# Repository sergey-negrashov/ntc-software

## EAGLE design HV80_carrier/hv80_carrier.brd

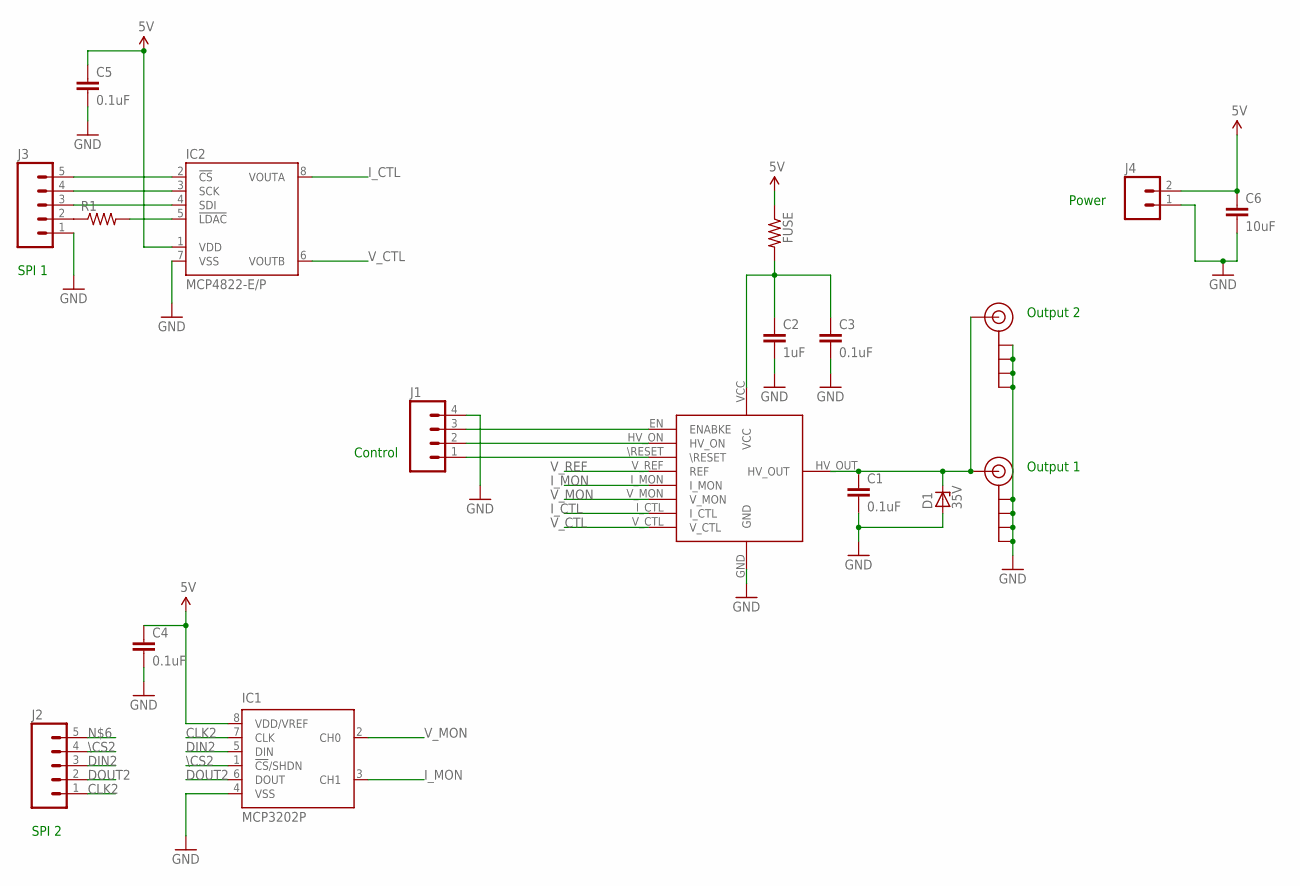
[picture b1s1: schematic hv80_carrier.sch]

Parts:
C1, C3, C4, C5: 0.1uF; 1206
C2: 1uF; 1206
C6: 10uF; 1206
D1: 35V; DO41Z10
FUSE: RESISTORPTH-1/4W; AXIAL-0.4
IC1: MCP3202P; DIL8
IC2: MCP4822-E/P; DIL08
J1: M04PTH; 1X04
J2, J3: M05PTH; 1X05
J4: M023.5MM; SCREWTERMINAL-3.5MM-2
J$1, J$2: SMA_EDGE; SMA-EDGE
R1: RESISTORPTH-1/4W; AXIAL-0.4
U$1: HV80

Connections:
5V: C4.1, C5.1, C6.1, FUSE.P$1 (1), IC1.8 (VDD/VREF), IC2.1 (VDD), J4.2
CLK2: IC1.7 (CLK), J2.1
DIN2: IC1.5 (DIN), J2.3
DOUT2: IC1.6 (DOUT), J2.2
GND: C1.2, C2.2, C3.2, C4.2, C5.2, C6.2, D1.A, IC1.4 (VSS), IC2.7 (VSS), J1.4, J3.1, J4.1, J$1.GND@0 (GND), J$1.GND@1 (GND), J$1.GND@2 (GND), J$1.GND@3 (GND), J$2.GND@0 (GND), J$2.GND@1 (GND), J$2.GND@2 (GND), J$2.GND@3 (GND), U$1.GND
I_CTL: IC2.8 (VOUTA), U$1.I_CTL
I_MON: IC1.3 (CH1), U$1.I_MON
unnamed: J1.1, U$1.\RESET
unnamed: J1.2, U$1.HV_ON
unnamed: J1.3, U$1.EN (ENABKE)
unnamed: C1.1, D1.C, J$1.SIG (SIGNAL), J$2.SIG (SIGNAL), U$1.HV_OUT
unnamed: J3.2, R1.P$1 (1)
unnamed: IC2.5 (!LDAC), R1.P$2 (2)
unnamed: C2.1, C3.1, FUSE.P$2 (2), U$1.VCC
SCK1: IC2.3 (SCK), J3.4
SDI1: IC2.4 (SDI), J3.3
V_CTL: IC2.6 (VOUTB), U$1.V_CTL
V_MON: IC1.2 (CH0), U$1.V_MON
V_REF: U$1.V_REF (REF)
\CS1: IC2.2 (!CS), J3.5
\CS2: IC1.1 (!CS!/SHDN), J2.4

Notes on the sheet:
SPI 1
SPI 2
Control
Power
Output 1
Output 2

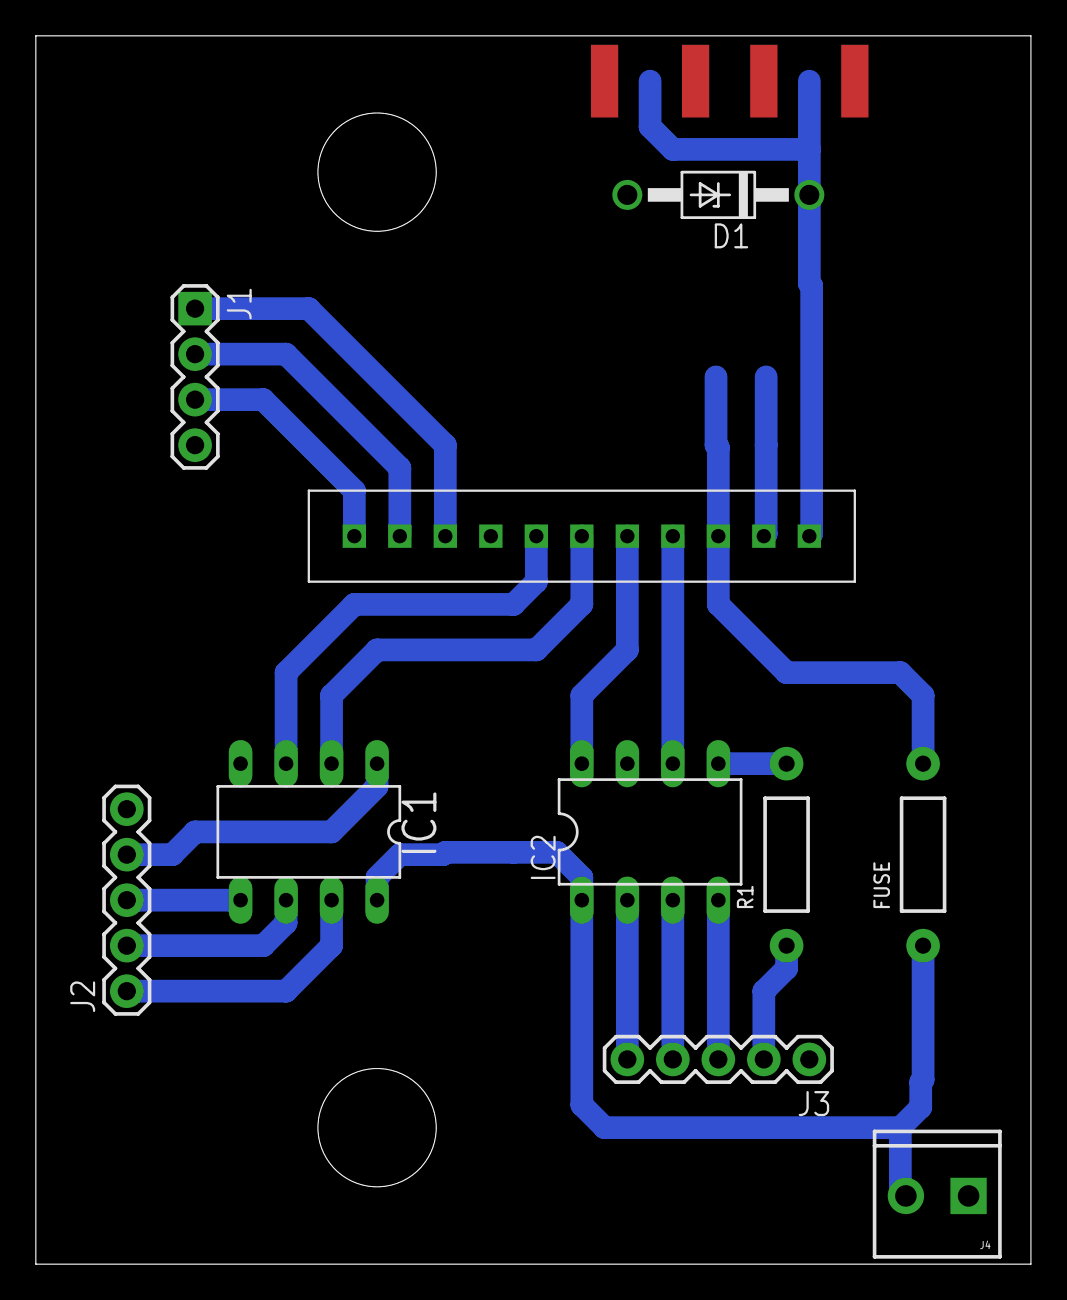
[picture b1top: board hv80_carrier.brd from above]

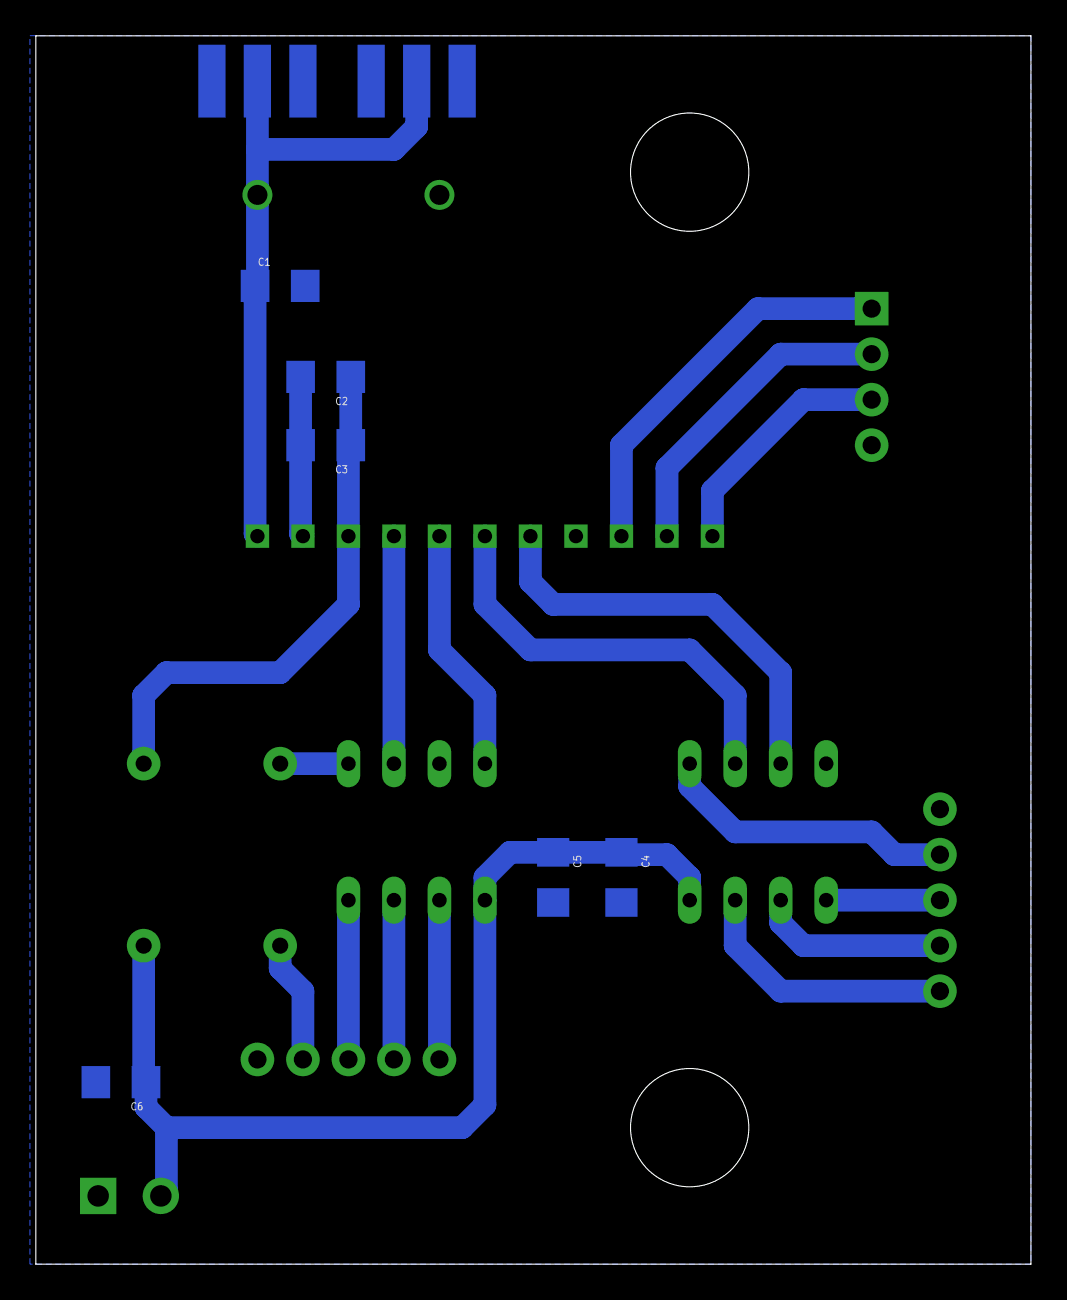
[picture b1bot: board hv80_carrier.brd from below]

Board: 2 copper layers, 55.5 x 68.6 mm, 18 parts (8 on the bottom side), 20 nets.

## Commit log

2016-09-22 Added motor controller class stub
2016-09-22 added README.md
2016-09-26 Update 1 moto.py
    Added slide information, pause, absolute movements, and looping movements.
2016-09-26 test file that prints commands
2016-10-10 Added the schematic and layout for the HV80 carrier board
2016-10-10 Added the simple dark_count analysis
2016-10-24 Added filter
2016-10-27 Added a DRS4 readout for NTC
2016-10-27 Made the motor code block untill the command is done.
2016-10-27 Added a script to cycle steper positions and take data.
2016-10-29 Dark count script for files read out on le Lecroy
2016-11-03 New readout code. New analisys code for the two SIPM tests
2016-11-14 Multithreaded analysis, Glenn format in DAQ, Sigh......
2016-11-18 Added a basic program to extract timing calibration values from a board.
2016-11-18 Fixed indexing bug in drs_ntc.cpp, was repeating same channel for all 4.
2016-11-18 Removed # from data lines.
2016-11-21 Switched drs_ntc.cpp to external trigger (to be verified)
2016-11-21 dog and pony show gui
2016-11-24 Added the net code
2016-11-25 Fixed external trigger
2016-11-25 Fixed the triggering
2016-11-26 Motor controll is done in cpp
2016-11-26 dog and pony show gui is ready
2016-11-26 added untracted file
2016-11-29 Fixed event numbers
2016-12-01 Added a temperature readout. Added a configuration file for the run.
2016-12-02 Testing slack integration
2017-04-05 Daisychained DRS4s with extrnal trigger
2017-04-07 Syncing repo up with -working version of 109 PC.
2017-04-12 Werking dual drs4
2017-06-13 Added a new version of readoutd. Got rid of Mpod and Pip support, since they are not needed for ntc. Added the motor controll.
2017-06-16 propogated motor control to python.
2017-06-16 forgot a file
2017-06-20 cleaned up repo
2017-06-21 Forgot to add headers. Fixed the gitignore.
2017-06-21 Initialize the event number to 0. We are not using card to pass the motor steps to readoutd in order to be able to run it backwards
2017-06-21 Changed the python api to use correct types. I wonder how long this was there..
2017-06-21 Changed the python api to use correct types
2017-06-21 Forgot a break statement
2017-06-21 test for the motor readoutd loop

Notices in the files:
parts and their libraries:
SparkFun-Passives: Licensing: Creative Commons ShareAlike 4.0 International - https://creativecommons.org/licenses/by-sa/4.0
